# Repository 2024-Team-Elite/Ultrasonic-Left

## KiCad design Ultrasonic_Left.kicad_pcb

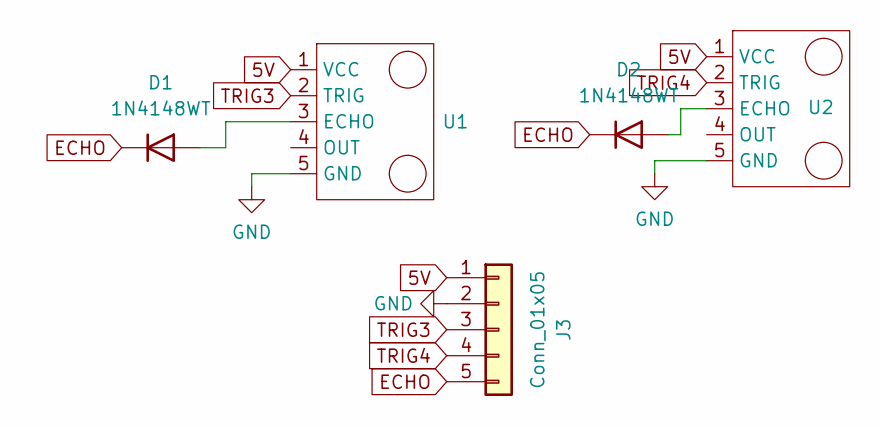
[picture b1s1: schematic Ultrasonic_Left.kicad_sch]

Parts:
D1, D2: 1N4148WT; D_SOD-123
J3: Conn_01x05; JST_XH_B5B-XH-A_1x05_P2.50mm_Vertical
U1, U2: PinHeader_1x05_P2.54mm_Vertical

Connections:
5V: J3.1, U1.1 (VCC), U2.1 (VCC)
ECHO: D1.1 (K), D2.1 (K), J3.5
GND: J3.2, U1.5 (GND), U2.5 (GND)
unnamed: D1.2 (A), U1.3 (ECHO)
unnamed: D2.2 (A), U2.3 (ECHO)
TRIG3: J3.3, U1.2 (TRIG)
TRIG4: J3.4, U2.2 (TRIG)

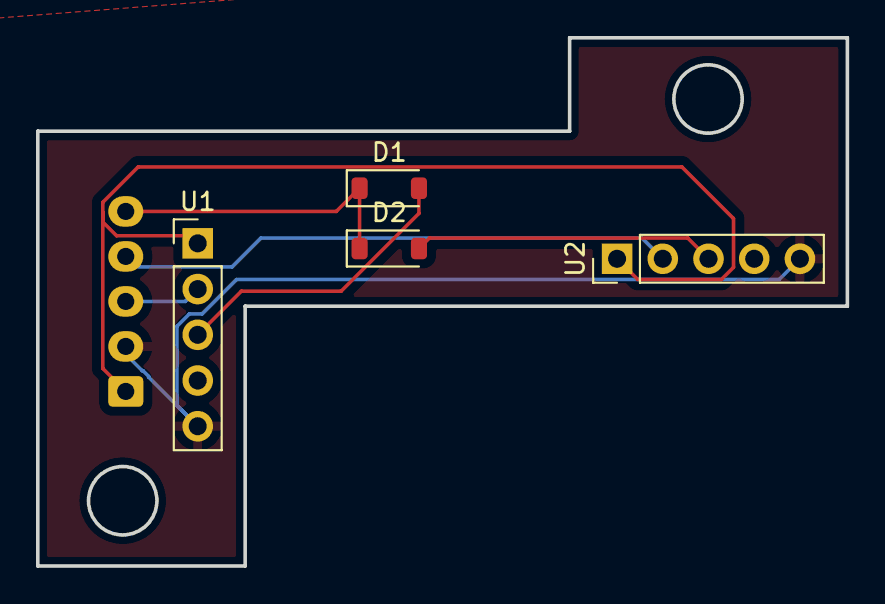
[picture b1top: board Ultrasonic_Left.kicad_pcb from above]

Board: 2 copper layers, 45.0 x 29.3 mm, 5 parts (1 on the bottom side), 7 nets.

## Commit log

2024-06-16 Finished
